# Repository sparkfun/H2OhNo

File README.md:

**Note:Retired Product**
This product has been retired from our catalog and is no longer for sale. This page is made available for those looking for datasheets and the simply curious.

H2OhNo
======

[ 
*H20hNo (DEV-12069)*](https://www.sparkfun.com/products/12069)

H2OhNo! is a small ATtiny development board that detects the presence of water and sets off an alarm.

Repository Contents
-------------------

* **/Firmware** - Example firmware for running the sensor
* **/Hardware** - All Eagle design files (.brd, .sch)

Documentation
-------------------
* **[Hookup Guide](https://learn.sparkfun.com/tutorials/h2ohno)** - Basic hookup guide for the H2OhNo

License Information
-------------------
The hardware is released under [Creative Commons Share-alike 3.0](http://creativecommons.org/licenses/by-sa/3.0/).  
All other code is open source so please feel free to do anything you want with it; you buy me a beer if you use this and we meet someday ([Beerware license](http://en.wikipedia.org/wiki/Beerware)).

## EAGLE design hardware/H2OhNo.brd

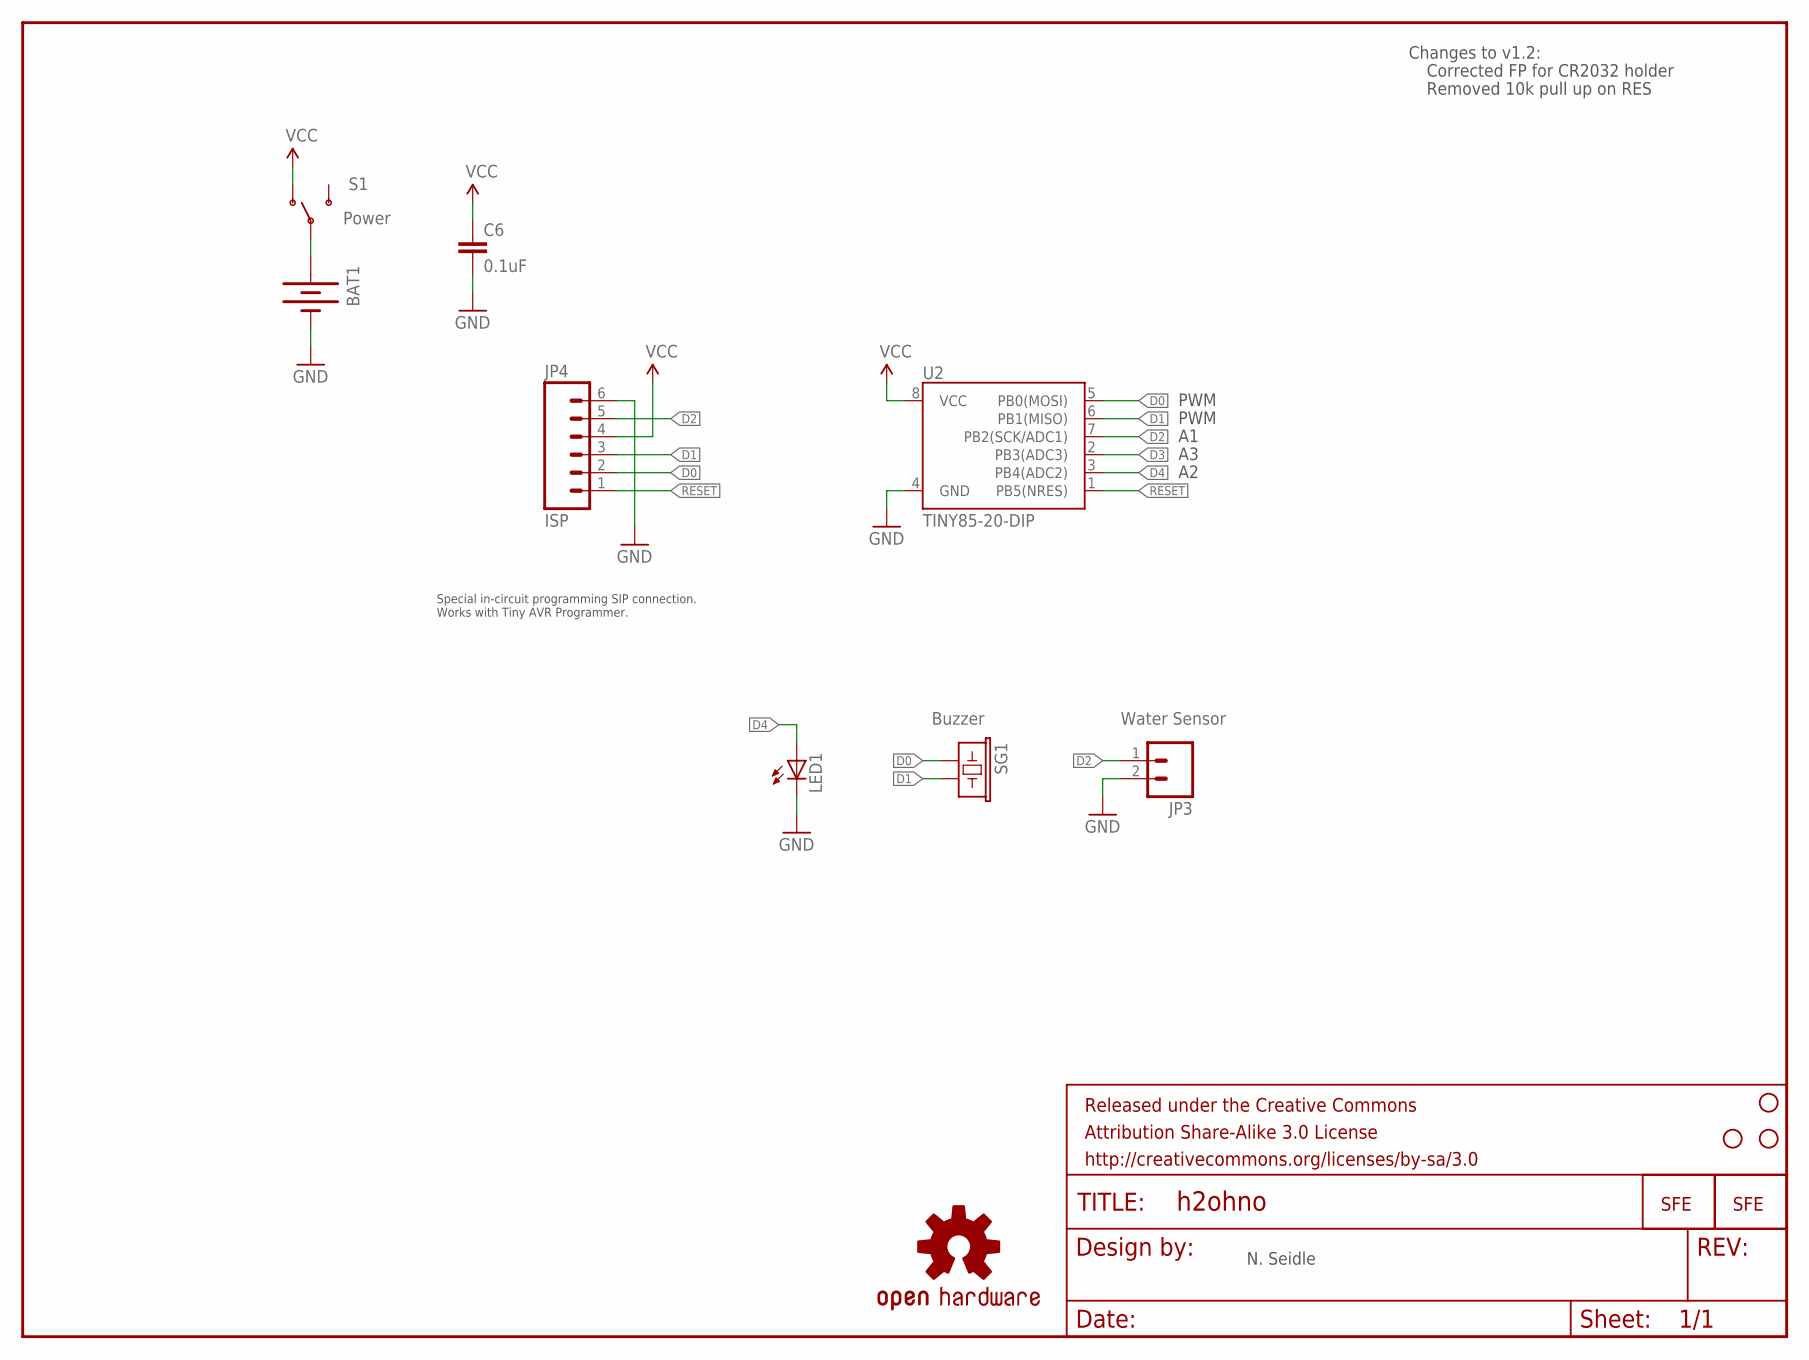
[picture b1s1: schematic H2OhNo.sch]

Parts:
BAT1: BATTERY20PTH; BATTCOM_20MM_PTH
C6: 0.1uF; CAP-PTH-SMALL2
FRAME2: FRAME-LETTER; CREATIVE_COMMONS
JP3: Water Sensor; 1X02
JP4: ISP; 1X06
LED1: LED5MM
S1: Power; SWITCH-SPDT
SG1: Buzzer; BUZZER-12MM
STANDOFF1, STANDOFF3, STANDOFF4: STAND-OFF
U2: TINY85-20-DIP; DIP08
U$1: LOGO-SFESK; SFE-LOGO-FLAME
U$4: OSHW-LOGOS; OSHW-LOGO-S
U$5: LOGO-SFENW2; SFE-NEW-WEB

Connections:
D0: JP4.2, SG1.+ (1), U2.5 (PB0(MOSI))
D1: JP4.3, SG1.- (2), U2.6 (PB1(MISO))
D2: JP3.1, JP4.5, U2.7 (PB2(SCK/ADC1))
D3: U2.2 (PB3(ADC3))
D4: LED1.A, U2.3 (PB4(ADC2))
GND: BAT1.2 (-), C6.2, JP3.2, JP4.6, LED1.K (C), U2.4 (GND)
unnamed: BAT1.1 (+), S1.2
RESET: JP4.1, U2.1 (PB5(NRES))
VCC: C6.1, JP4.4, S1.1 (O), U2.8 (VCC)

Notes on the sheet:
N. Seidle
Changes to v1.2:
PWM
Corrected FP for CR2032 holder
Removed 10k pull up on RES
Special in-circuit programming SIP connection. Works with Tiny AVR Programmer.

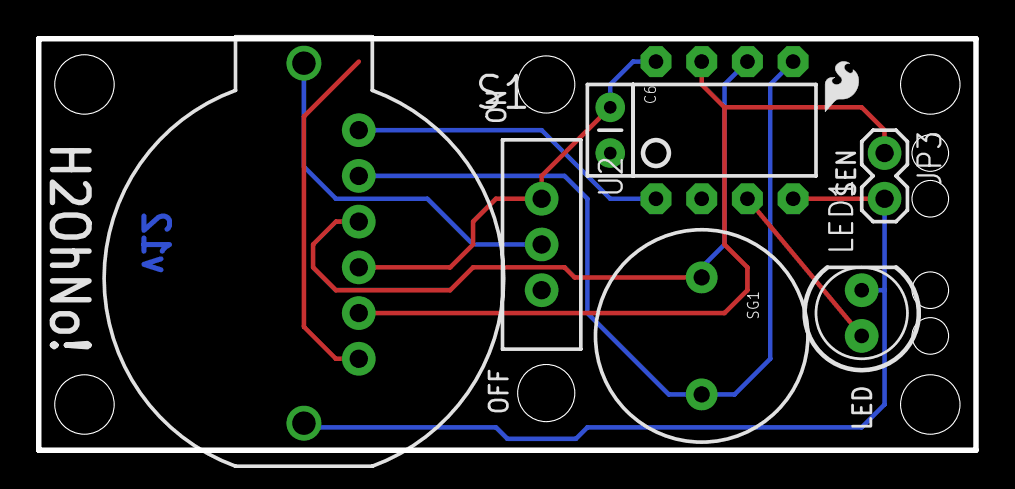
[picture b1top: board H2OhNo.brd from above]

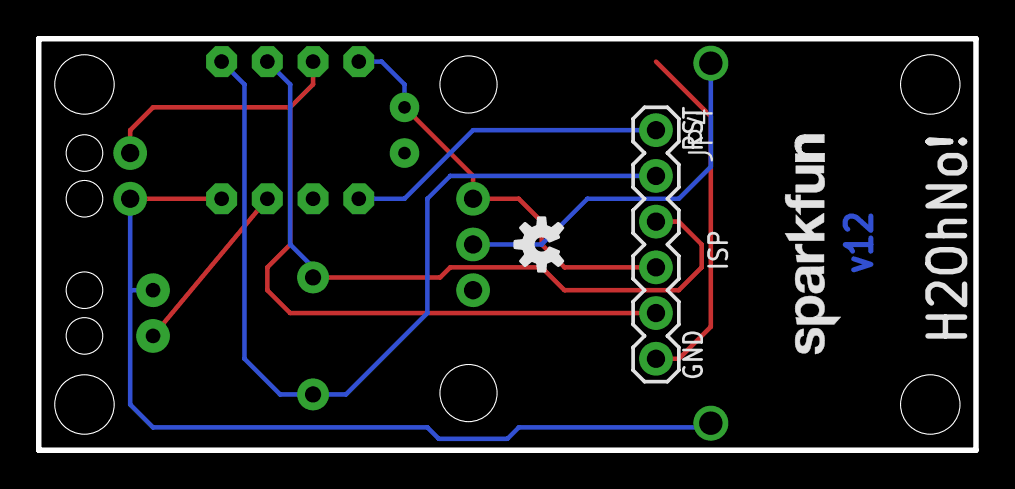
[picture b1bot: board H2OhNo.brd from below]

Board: 2 copper layers, 52.1 x 22.9 mm, 16 parts (3 on the bottom side), 8 nets.

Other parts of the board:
STANDOFF2: STAND-OFF

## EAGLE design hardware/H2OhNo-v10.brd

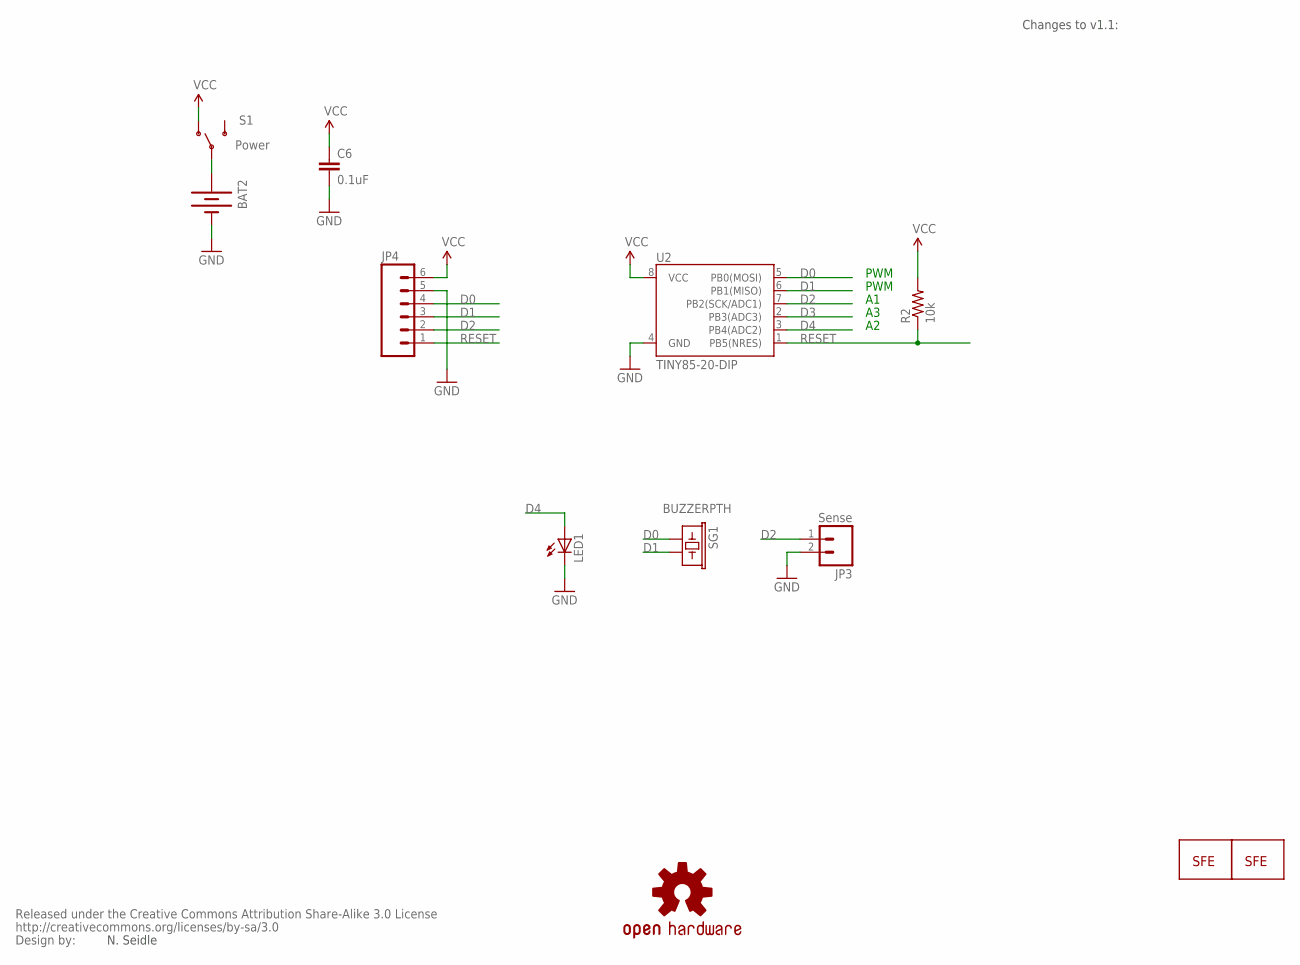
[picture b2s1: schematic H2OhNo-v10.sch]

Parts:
BAT2: BATTERY20PTH; BATTCOM_20MM_PTH
C6: 0.1uF; CAP-PTH-SMALL2
JP3: Sense; 1X02
JP4: M06SIP; 1X06
LED1: LED5MM
R2: 10k; AXIAL-0.3
S1: Power; SWITCH-SPDT
SG1: BUZZERPTH; BUZZER-12MM
U2: TINY85-20-DIP; DIP08
U$1: LOGO-SFESK; SFE-LOGO-FLAME
U$2: CREATIVE_COMMONS
U$4: OSHW-LOGOS; OSHW-LOGO-S
U$5: LOGO-SFENW2; SFE-NEW-WEB

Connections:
D0: JP4.4, SG1.+ (1), U2.5 (PB0(MOSI))
D1: JP4.3, SG1.- (2), U2.6 (PB1(MISO))
D2: JP3.1, JP4.2, U2.7 (PB2(SCK/ADC1))
D3: U2.2 (PB3(ADC3))
D4: LED1.A, U2.3 (PB4(ADC2))
GND: BAT2.2 (-), C6.2, JP3.2, JP4.5, LED1.K (C), U2.4 (GND)
unnamed: BAT2.1 (+), S1.2
RESET: JP4.1, R2.P$1 (1), U2.1 (PB5(NRES))
VCC: C6.1, JP4.6, R2.P$2 (2), S1.1 (O), U2.8 (VCC)

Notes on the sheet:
N. Seidle
Changes to v1.1:
PWM

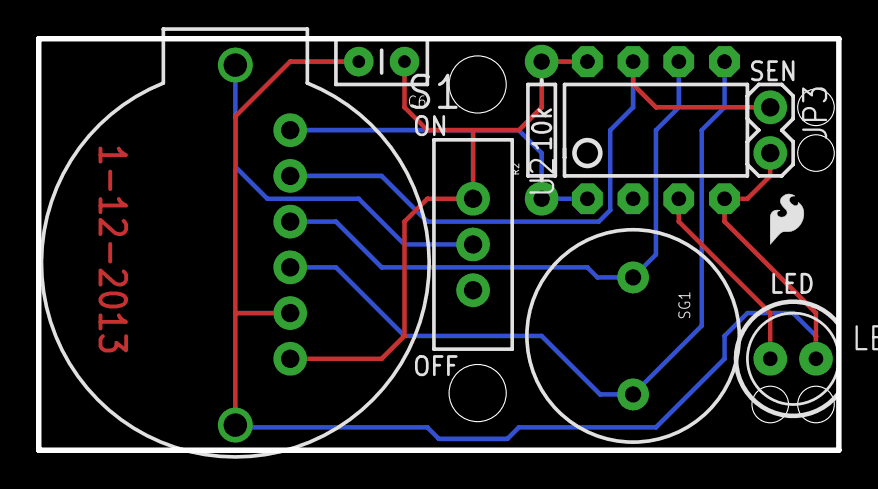
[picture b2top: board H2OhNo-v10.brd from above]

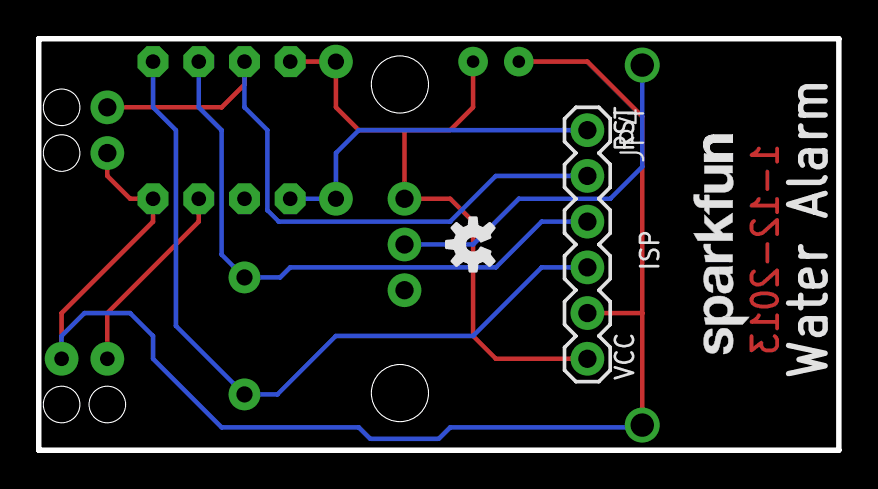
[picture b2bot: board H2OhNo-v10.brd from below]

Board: 2 copper layers, 44.5 x 22.9 mm, 13 parts (3 on the bottom side), 8 nets.

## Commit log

2013-04-03 Pushing version 1 of the files.
    This version works. Need to increase isolation to 0.012.
2013-09-23 Added version #. Fixed file naming. Removed 10k on RES.
    Fixed footprint on CR2032 as well.
2013-09-23 Remove legacy code. Works under Arduino v1.0.5.
2013-09-23 Modified 6-pin SIP header for FTDI compatibility
    It's not serial, but you should be able to bit-bang serial out the
    MOSI/MISO lines and use an FTDI on the programming header. Good for
    debugging.
2013-09-23 Hardware changes to address issues on github.
    Moved 0.1uF cap closer to IC. Added standoffs. Increased board size.
    Moved LED and sense towards end of board.
2013-10-14 Added power saving to main firmware. Should run for 150+ days.
    Got current usage down to ~50uA. Should run for 166 days on a CR2032.
2013-10-20 Creating and updating example code for tutorial hook up guide.
2013-11-15 Adding version number to schematic
2013-11-22 Update README.md
    Adding in product URLs
2013-12-10 Adding Christmas Tree alarm
2013-12-10 Adding status LED to Xmas example
2018-03-28 Updated readme to reflect retired product
    Added note to reflect retired product
2018-03-28 Updated ReadMe to contain link to hookup guide
    Added link to sparkfun hookup guide for future reference.

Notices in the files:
parts and their libraries:
SparkFun: Released under the Creative Commons Attribution Share-Alike 3.0 License
SparkFun-DigitalIC: Licensing: CC v3.0 Share-Alike You are welcome to use this library for commercial purposes.
SparkFun-Aesthetics: Released under the Creative Commons
